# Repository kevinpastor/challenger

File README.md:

# Challenger

A 35-key gaming keypad powered by ZMK.

## Features

- 35 MX-compatible keys
- Wireless (nice!nano)
- nice!view display
- Hotswap sockets

## Bill of Materials

### PCB

| Qty | Part | Description |
|-----|------|-------------|
| 1 | Challenger PCB | |
| 35 | MX switches (of your choice) |  |
| 35 | Kailh MX hot-swap sockets | Switch sockets |
| 35 | 1N4148W diodes | SMD switch diodes |
| 1 | [nice!nano v2](https://nicekeyboards.com/nice-nano/) | Wireless microcontroller |
| 2 | Mill-Max [315-43-112-41-003000](https://www.digikey.ca/en/products/detail/digikey-va/315-43-112-41-003000/4455232) | Female header, 12-pin, microcontroller socket |
| 2 | Mill-Max [350-10-112-00-006000](https://www.digikey.ca/en/products/detail/digikey-va/350-10-112-00-006000/4456133) | Pin header, 12-pin, microcontroller socket |
| 1 | Panasonic [EVQ-PUL02K](https://www.digikey.ca/en/products/detail/panasonic-industry/EVQ-PUL02K/286340) | Tactile switch, as the reset button |
| 1 | Alps Alpine [SSSS811101](https://www.digikey.ca/en/products/detail/alps-alpine/SSSS811101/19529062) | Slide switch, as the power switch |
| 1 | [3.7v 110mAh 301230 LiPo battery](https://www.aliexpress.com/item/1005005348368664.html) | Positive terminal must be on the right side of the connector
| 1 | JST [S2B-PH-K-S](https://www.digikey.ca/en/products/detail/jst-sales-america-inc/S2B-PH-K-S/926626) | Battery connector, 2-pin |

The [EVQ-PUJ02K](https://www.digikey.ca/en/products/detail/panasonic-industry/EVQ-PUJ02K/286338), the [EVQ-PUA02K](https://www.digikey.ca/en/products/detail/panasonic-industry/EVQ-PUA02K/286334), or the [EVQ-PUC02K](https://www.digikey.ca/en/products/detail/panasonic-industry/EVQ-PUC02K/286336) could be used instead for the reset button, since they only differ in operating force or boss (aligning plastic tab on the underside).

The battery connector model number can have a different last letter or no at all (e.g. [S2B-PH-K-K](https://www.digikey.ca/en/products/detail/jst-sales-america-inc/S2B-PH-K-K/27506616), S2B-PH-K-H, [S2B-PH-K](https://www.digikey.ca/en/products/detail/jst-sales-america-inc/S2B-PH-K/28540441)), which only represents its color.

### Case

| Qty | Part | Description |
|-----|------|-------------|
| 1 | Switch plate PCB | |
| 1 | Bottom plate PCB | |
| 4 | M2 x 7 mm standoffs | Case standoffs |
| 8 | M2 x 5 mm screws | Case screws |

M2 x 4 mm screws might be able to be used instead of the M2 x 5 mm screws.

### Display

> The display cover has not been designed yet. Some parts listed are for future reference.

| Qty | Part | Description |
|-----|------|-------------|
| 1 | [nice!view](https://nicekeyboards.com/nice-view) | Display |
| 2 | M2 x 10 mm standoffs | Cover standoffs |
| 2 | M2 x 5 mm screws | Cover standoff screws |

M2 x 4 mm screws might be able to be used instead of the M2 x 5 mm screws.

## Build

See the [build guide](docs/index.md) for step-by-step assembly instructions.

## Firmware

Built with [ZMK](https://zmk.dev).

## License

[MIT](LICENSE)

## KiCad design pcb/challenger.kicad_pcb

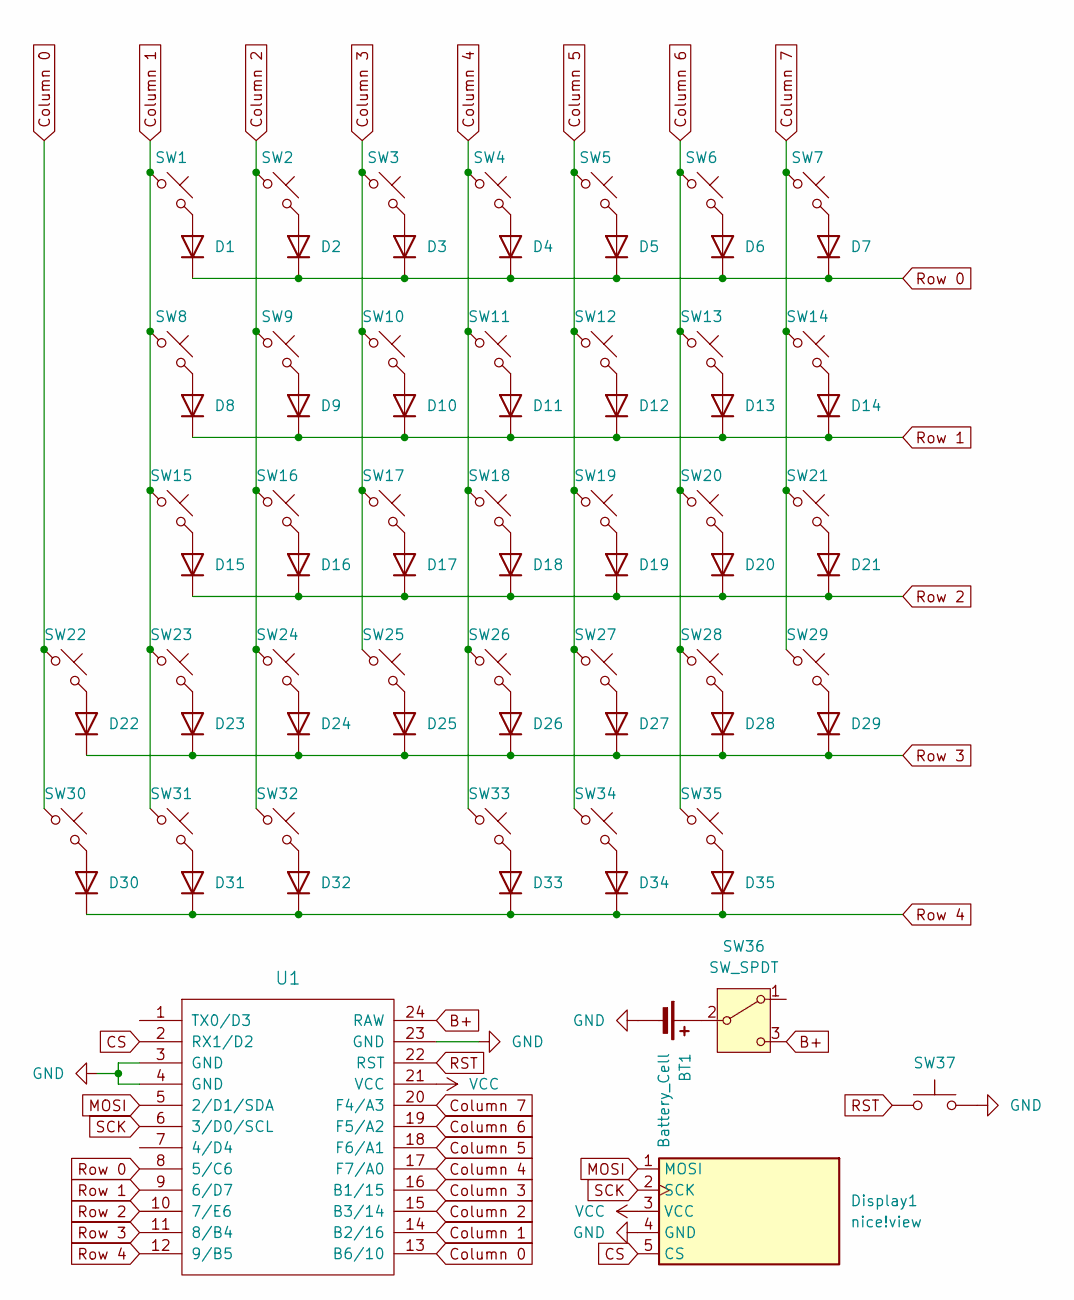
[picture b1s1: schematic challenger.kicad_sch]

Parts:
BT1: Battery_Cell; JST_PH_S2B-PH-K_1x02_P2.00mm_Horizontal
D1, D2, D3, D4, D5, D6, D7, D8, D9, D10, D11, D12, D13, D14, D15, D16, D17, D18, D19, D20, D21, D22, D23, D24, D25, D26, D27, D28, D29, D30, D31, D32, D33, D34, D35: 1N4148; D_SOD-123
Display1: nice!view; nice_view
SW1, SW2, SW3, SW4, SW5, SW6, SW7, SW8, SW9, SW10, SW11, SW12, SW13, SW14, SW15, SW16, SW17, SW18, SW19, SW20, SW21, SW22, SW23, SW24, SW25, SW26, SW27, SW28, SW29, SW30, SW31, SW32, SW33, SW34: SW_Push_45deg; Hotswap_MX_1.00u
SW35: SW_Push_45deg; Hotswap_MX_1.50u
SW36: SW_SPDT; SW_SPDT_PCM12
SW37: SW_Push; Panasonic_EVQPUL_EVQPUC
U1: ProMicro; nice_nano

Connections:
B+: SW36.3 (C), U1.24 (RAW)
CS: Display1.5 (CS), U1.2 (RX1/D2)
Column 0: SW22.1, SW30.1, U1.13 (B6/10)
Column 1: SW1.1, SW8.1, SW15.1, SW23.1, SW31.1, U1.14 (B2/16)
Column 2: SW2.1, SW9.1, SW16.1, SW24.1, SW32.1, U1.15 (B3/14)
Column 3: SW3.1, SW10.1, SW17.1, SW25.1, U1.16 (B1/15)
Column 4: SW4.1, SW11.1, SW18.1, SW26.1, SW33.1, U1.17 (F7/A0)
Column 5: SW5.1, SW12.1, SW19.1, SW27.1, SW34.1, U1.18 (F6/A1)
Column 6: SW6.1, SW13.1, SW20.1, SW28.1, SW35.1, U1.19 (F5/A2)
Column 7: SW7.1, SW14.1, SW21.1, SW29.1, U1.20 (F4/A3)
GND: BT1.2 (-), Display1.4 (GND), SW37.2, U1.3 (GND), U1.4 (GND), U1.23 (GND)
MOSI: Display1.1 (MOSI), U1.5 (2/D1/SDA)
unnamed: BT1.1 (+), SW36.2 (B)
unnamed: D1.2 (A), SW1.2
unnamed: D2.2 (A), SW2.2
unnamed: D3.2 (A), SW3.2
unnamed: D4.2 (A), SW4.2
unnamed: D5.2 (A), SW5.2
unnamed: D6.2 (A), SW6.2
unnamed: D7.2 (A), SW7.2
unnamed: D8.2 (A), SW8.2
unnamed: D9.2 (A), SW9.2
unnamed: D10.2 (A), SW10.2
unnamed: D11.2 (A), SW11.2
unnamed: D12.2 (A), SW12.2
unnamed: D13.2 (A), SW13.2
unnamed: D14.2 (A), SW14.2
unnamed: D15.2 (A), SW15.2
unnamed: D16.2 (A), SW16.2
unnamed: D17.2 (A), SW17.2
unnamed: D18.2 (A), SW18.2
unnamed: D19.2 (A), SW19.2
unnamed: D20.2 (A), SW20.2
unnamed: D21.2 (A), SW21.2
unnamed: D22.2 (A), SW22.2
unnamed: D23.2 (A), SW23.2
unnamed: D24.2 (A), SW24.2
unnamed: D25.2 (A), SW25.2
unnamed: D26.2 (A), SW26.2
unnamed: D27.2 (A), SW27.2
unnamed: D28.2 (A), SW28.2
unnamed: D29.2 (A), SW29.2
unnamed: D30.2 (A), SW30.2
unnamed: D31.2 (A), SW31.2
unnamed: D32.2 (A), SW32.2
unnamed: D33.2 (A), SW33.2
unnamed: D34.2 (A), SW34.2
unnamed: D35.2 (A), SW35.2
RST: SW37.1, U1.22 (RST)
Row 0: D1.1 (K), D2.1 (K), D3.1 (K), D4.1 (K), D5.1 (K), D6.1 (K), D7.1 (K), U1.8 (5/C6)
Row 1: D8.1 (K), D9.1 (K), D10.1 (K), D11.1 (K), D12.1 (K), D13.1 (K), D14.1 (K), U1.9 (6/D7)
Row 2: D15.1 (K), D16.1 (K), D17.1 (K), D18.1 (K), D19.1 (K), D20.1 (K), D21.1 (K), U1.10 (7/E6)
Row 3: D22.1 (K), D23.1 (K), D24.1 (K), D25.1 (K), D26.1 (K), D27.1 (K), D28.1 (K), D29.1 (K), U1.11 (8/B4)
Row 4: D30.1 (K), D31.1 (K), D32.1 (K), D33.1 (K), D34.1 (K), D35.1 (K), U1.12 (9/B5)
SCK: Display1.2 (SCK), U1.6 (3/D0/SCL)
VCC: Display1.3 (VCC), U1.21 (VCC)

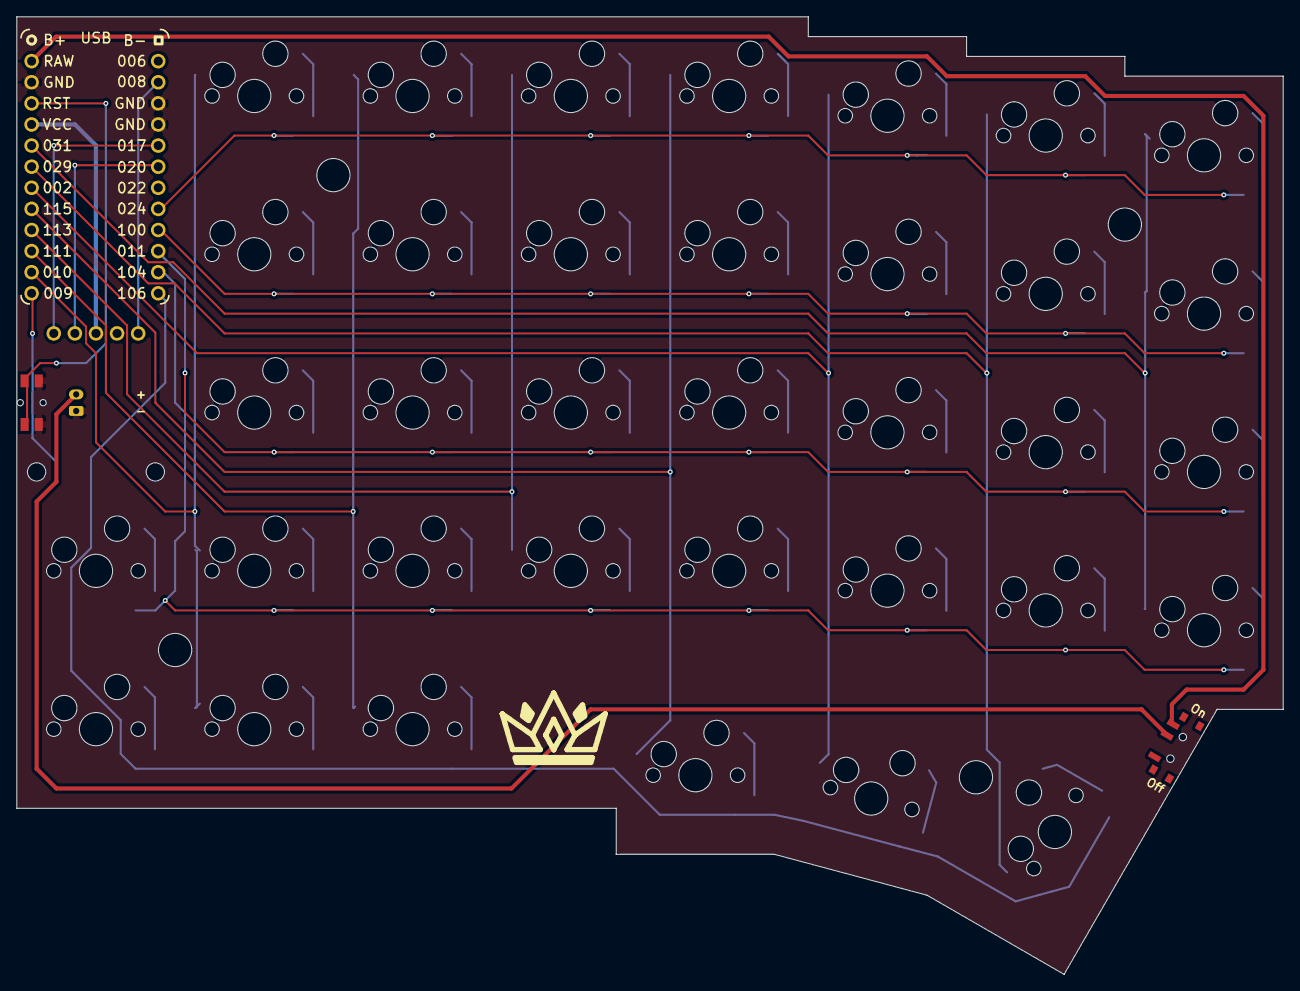
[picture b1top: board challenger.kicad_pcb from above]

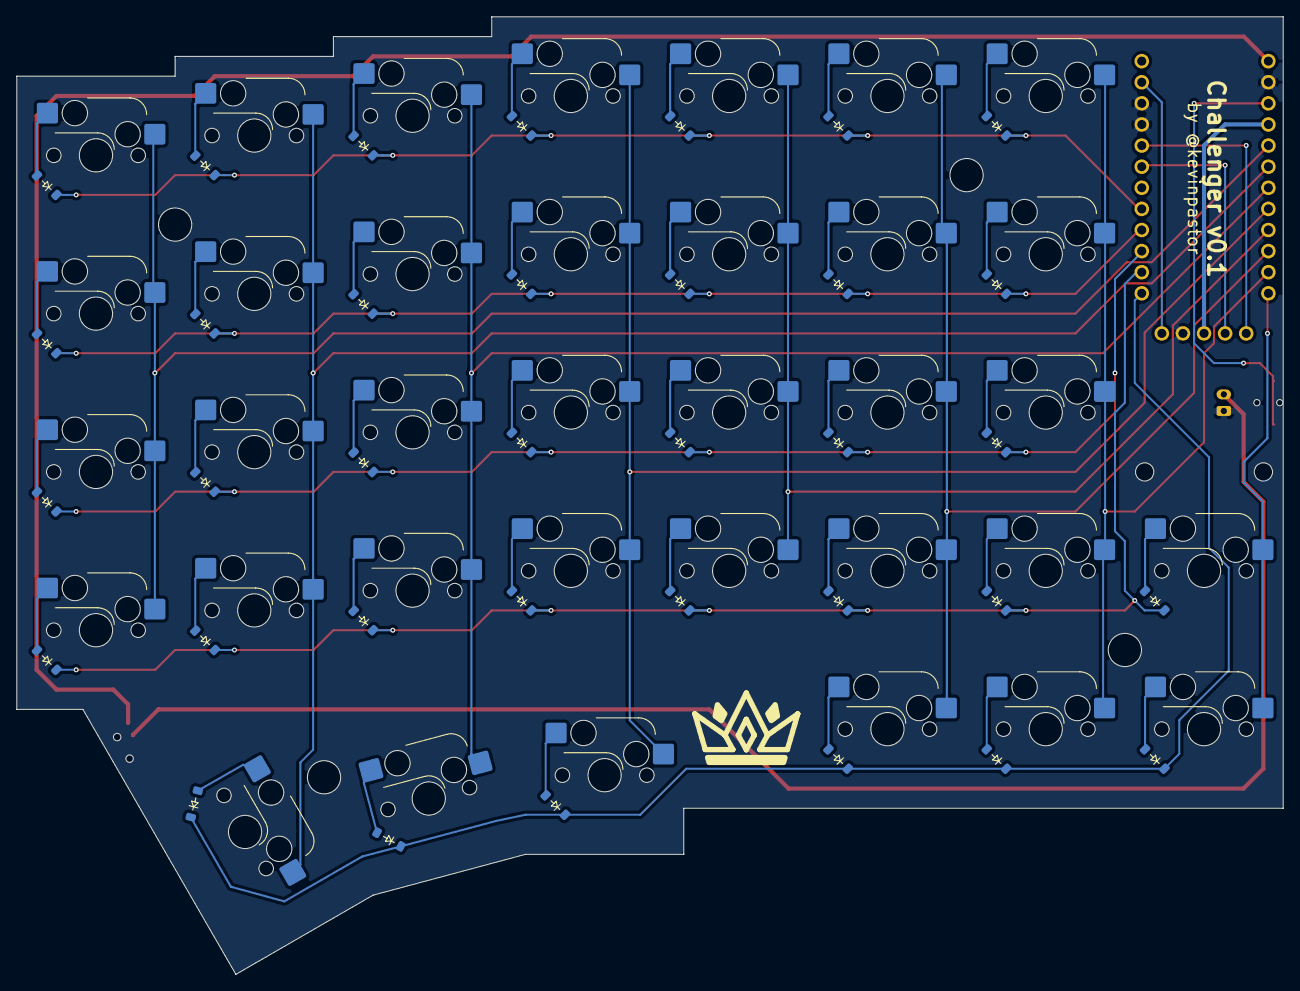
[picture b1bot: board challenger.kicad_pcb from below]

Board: 2 copper layers, 152.4 x 115.2 mm, 75 parts (36 on the bottom side), 56 nets.
